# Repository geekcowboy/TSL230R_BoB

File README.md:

View this project on [CADLAB.io](https://cadlab.io/project/1936). 

# TSL230R_BoB
Breakout Board for the TSL230R Light-to-Frequnecy Converter

Order PCB from OSH Park: https://oshpark.com/shared_projects/PTr8h8xv

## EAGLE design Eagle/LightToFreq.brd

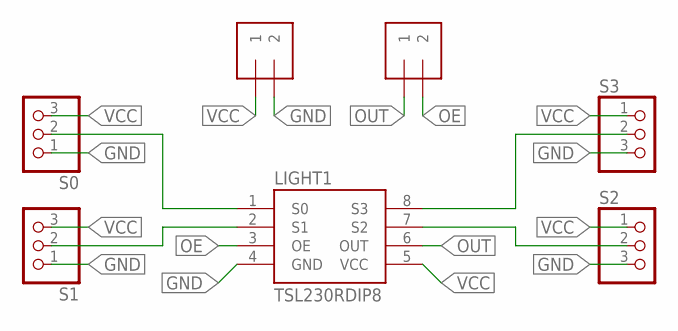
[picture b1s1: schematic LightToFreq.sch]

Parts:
J1, J2: 1X2-3.5MM
LIGHT1: TSL230RDIP8; DIP8
S0, S1, S2, S3: PINHD-1X3CB; 1X03-CLEANBIG

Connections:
GND: J1.2, LIGHT1.4 (GND), S0.1, S1.1, S2.3, S3.3
unnamed: LIGHT1.1 (S0), S0.2
unnamed: LIGHT1.2 (S1), S1.2
unnamed: LIGHT1.8 (S3), S3.2
unnamed: LIGHT1.7 (S2), S2.2
OE: J2.2, LIGHT1.3 (OE)
OUT: J2.1, LIGHT1.6 (OUT)
VCC: J1.1, LIGHT1.5 (VCC), S0.3, S1.3, S2.1, S3.1

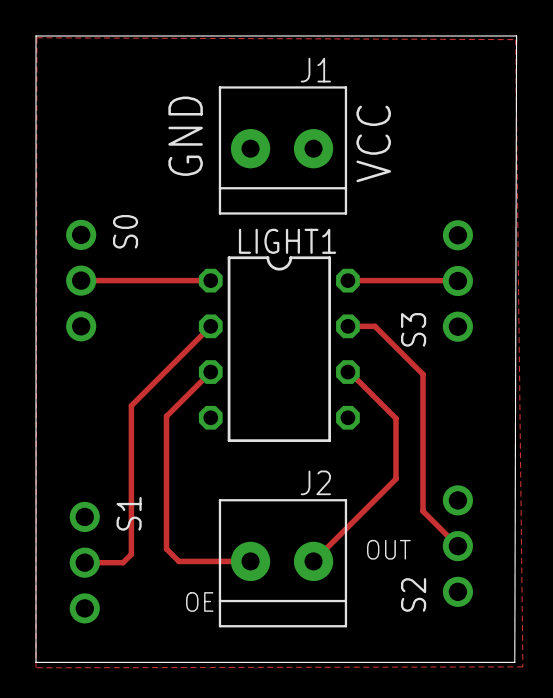
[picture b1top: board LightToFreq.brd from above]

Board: 2 copper layers, 26.7 x 34.8 mm, 7 parts (0 on the bottom side), 8 nets.

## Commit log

2015-10-31 Init Release
    TSL230R Breakout Board
2019-07-01 Backlink to CADLAB.io has been added.
